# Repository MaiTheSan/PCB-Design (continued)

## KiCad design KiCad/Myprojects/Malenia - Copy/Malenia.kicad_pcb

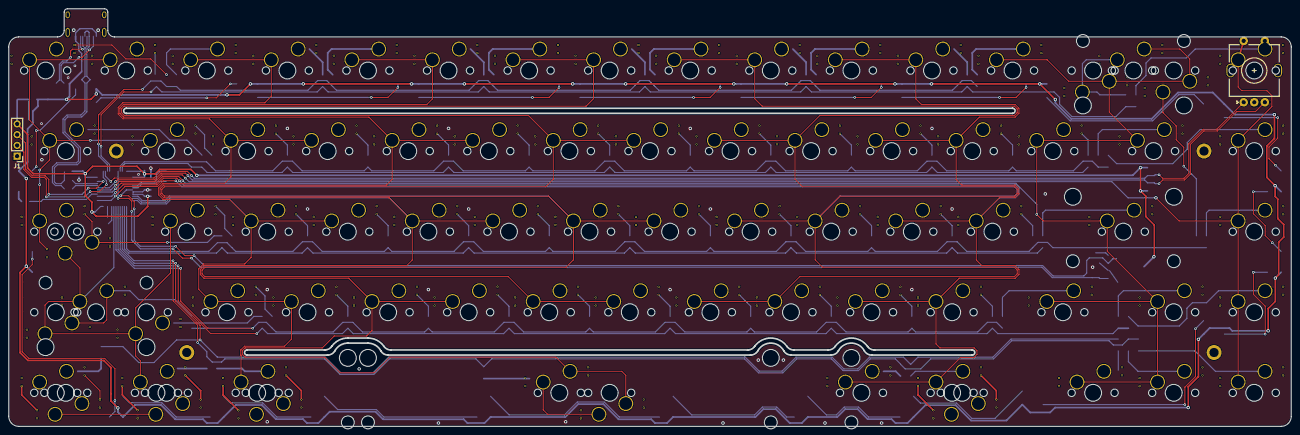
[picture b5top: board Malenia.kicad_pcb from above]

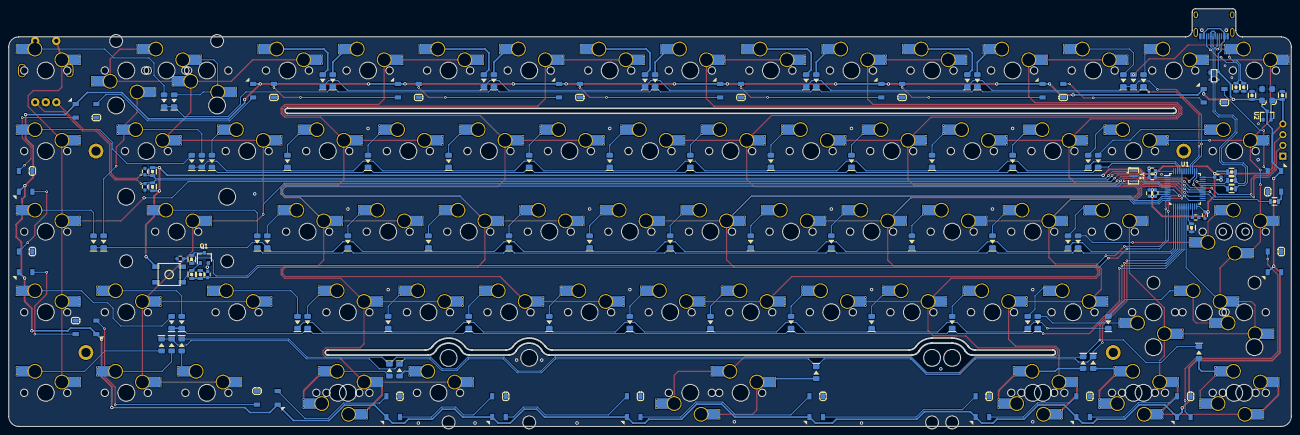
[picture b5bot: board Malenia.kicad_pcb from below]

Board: 2 copper layers, 303.2 x 98.7 mm, 207 parts (124 on the bottom side), 130 nets.

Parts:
C1, C2, C3, C4, C5, C9, C11, C12: 0.1uF; C_0603
C6: 1uF; C_0603
C7, C8: 1uF; CP_EIA-3216
C10: 10uF (5%); C_0603
C13: 4.7uF; C_0603
D1, D2, D3, D4, D5, D6, D7, D8, D9, D10, D11, D12, D13, D14, D15, D16, D17, D18, D19, D20, D21, D22, D23, D24, D25, D26, D27, D28, D29, D30, D31, D32, D33, D34, D35, D36, D37, D38, D39, D40, D41, D42, D43, D44, D45, D46, D47, D48, D49, D50, D51, D52, D53, D54, D55, D56, D57, D58, D59, D62, D65, D66, D67, D68, D69, D70, D71, D72, D73: SOD123; DIODE_1206_SawnsProjects
D75, D76, D77, D78, D79, D80, D81, D82, D83, D84, D85, D86, D87, D88, D89, D90, D91, D92, D93, D94, D95: WS2812B; LED_WS2812B_PLCC4_5.0x5.0mm_P3.2mm
H1, H2, H3, H4: MountingHole; MountingHole_2.2mm_M2_ISO7380_Pad
J1: Conn_01x04_Female; PinHeader_1x04_P2.54mm_Vertical
MX1, MX2, MX3, MX4, MX5, MX6, MX7, MX8, MX9, MX10, MX11, MX12, MX13, MX14, MX15, MX18, MX19, MX20, MX21, MX22, MX23, MX24, MX25, MX26, MX27, MX28, MX29, MX30, MX31, MX32, MX33, MX34, MX35, MX36, MX37, MX38, MX41, MX42, MX44, MX45, MX46, MX47, MX48, MX49, MX50, MX51, MX52, MX53, MX55, MX57, MX63, MX66, MX67, MX68, MX70, MX71, MX72, MX73: MX-1U; MXOnly-1U-Hotswap-Sawns
MX16, MX40, MX62, MX64, MX65: MX-1.5U; MXOnly-1.5U-Hotswap-Sawns
MX17, MX54: MX-1.75U; MXOnly-1.75U-Hotswap-Sawns
MX39: MX-2.25U; MXOnly-2.25U-Hotswap-ReversedStabilizers-Sawns
MX43, MX56, MX58, MX59, MX60, MX77, MX78: MX-1.25U; MXOnly-1.25U-Hotswap-Sawns
MX61: MX-6.25U; MXOnly-7U-Hotswap-Sawns
MX69: MX-6.25U; MXOnly-6.25U-Hotswap-ReversedStabilizers-Sawns
MX75: MX-2.25U; MXOnly-2.25U-Hotswap-Sawns
MX76: MX-2U; MXOnly-2U-Hotswap-Sawns
Q1: DTC123J; SC-59
R1, R2: 100K; R_0805
R3: 100R; R_0805
R4: 330k (1%); R_0805
R5: 1M (1%); R_0805
R6, R7: 22R; R_0805
R8, R9: 5.1k; R_0805
R10: 1.5k; R_0805
R11, R14: 330R; R_0805
R12, R13: 10k; R_0805
SW1: SW_Push; SKQGADE010
SW2: Rotary_Encoder_Switch; RotaryEncoder_Alps_EC11E-Switch_Vertical_H20mm_Center
U1: STM32F0X2/STM32F303; LQFP-48_7x7mm_P0.5mm
U2: MCP1700-3302E / MCP1703A-3302 (SOT23); SOT-23
U3: PRTR5V0U2X; SOT143B
USB1: HRO-TYPE-C-31-M-12-Type-C; HRO-TYPE-C-31-M-12-Assembly
Y1: 8Mhz; Resonator_SMD_muRata_CSTxExxV-3Pin_3.0x1.1mm

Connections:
+3V3: C1.1, C2.1, C3.1, C4.1, C5.1, C6.1, C8.1, J1.4, R2.1, R10.2, R12.1, R13.2, SW1.1, U1.1, U1.9, U1.24, U1.36, U1.48, U2.2
+5V: C7.1, D75.1, D76.1, D77.1, D78.1, D79.1, D80.1, D81.1, D82.1, D83.1, D84.1, D85.1, D86.1, D87.1, D88.1, D89.1, D90.1, D91.1, D92.1, D93.1, D94.1, D95.1, R1.1, U2.3, U3.4, USB1.2, USB1.11
/MCU/A+: R7.1, R10.1, U3.2, USB1.6, USB1.8
/MCU/A-: R6.2, U3.3, USB1.5, USB1.7
Boot0: C10.2, R4.1, R5.2, U1.44
C0: MX1.1, MX2.1, MX16.1, MX17.2, MX18.1, MX19.1, MX43.2, MX44.2, MX56.1, MX58.1, MX59.1, MX62.2, MX63.2, MX75.1, U1.19
C1: MX3.1, MX4.1, MX20.1, MX21.1, MX22.1, MX23.1, MX45.1, MX46.1, MX60.1, MX64.2, U1.12
C2: MX5.1, MX6.1, MX24.1, MX25.1, MX26.1, MX27.1, MX47.1, MX48.1, MX61.1, MX69.2, U1.11
C3: MX7.1, MX8.1, MX28.1, MX29.1, MX30.1, MX31.1, MX49.1, MX50.1, U1.10
C4: MX9.1, MX10.1, MX32.1, MX33.1, MX34.1, MX35.1, MX51.1, MX52.1, U1.25
C5: MX11.1, MX36.1, MX37.1, MX53.1, MX65.1, MX70.1, MX71.1, MX72.1, MX73.1, MX77.1, MX78.2, U1.27
C6: MX12.1, MX13.1, MX14.1, MX38.1, MX39.1, MX40.1, MX54.1, MX55.1, MX66.1, MX67.1, MX76.2, U1.29
C7: MX15.1, MX41.1, MX42.1, MX57.1, MX68.1, SW2.S2, U1.30
D+: R7.2, U1.33
D-: R6.1, U1.32
DOUT1: D83.2, D84.4
DOUT2: D92.2, D93.4
EC_A: C12.1, R13.1, SW2.A, U1.38
EC_B: C11.2, R12.2, SW2.B, U1.31
GND: C1.2, C2.2, C3.2, C4.2, C5.2, C6.2, C7.2, C8.2, C9.2, C10.1, C11.1, C12.2, C13.2, D75.3, D76.3, D77.3, D78.3, D79.3, D80.3, D81.3, D82.3, D83.3, D84.3, D85.3, D86.3, D87.3, D88.3, D89.3, D90.3, D91.3, D92.3, D93.3, D94.3, D95.3, J1.1, Q1.2, R1.2, R2.2, R5.1, R8.2, R9.1, R14.2, SW2.C, U1.8, U1.23, U1.35, U1.47, U2.1, U3.1, USB1.1, USB1.12, USB1.13, Y1.2
MX15: D40.2, MX15.2, SW2.S1
NRST: C9.1, R3.1, U1.7
unnamed: C13.1, U1.22
unnamed: D1.2, MX1.2
unnamed: D2.2, MX16.2
unnamed: D3.2, MX17.1, MX56.2
unnamed: D4.2, MX2.2
unnamed: D5.2, MX18.2
unnamed: D6.2, MX19.2
unnamed: D7.2, MX3.2
unnamed: D8.2, MX20.2
unnamed: D9.2, MX21.2
unnamed: D10.2, MX4.2
unnamed: D11.2, MX22.2
unnamed: D12.2, MX23.2
unnamed: D13.2, MX5.2
unnamed: D14.2, MX24.2
unnamed: D15.2, MX25.2
unnamed: D16.2, MX6.2
unnamed: D17.2, MX26.2
unnamed: D18.2, MX27.2
unnamed: D19.2, MX7.2
unnamed: D20.2, MX28.2
unnamed: D21.2, MX29.2
unnamed: D22.2, MX8.2
unnamed: D23.2, MX30.2
unnamed: D24.2, MX31.2
unnamed: D25.2, MX9.2
unnamed: D26.2, MX32.2
unnamed: D27.2, MX33.2
unnamed: D28.2, MX10.2
unnamed: D29.2, MX34.2
unnamed: D30.2, MX35.2
unnamed: D31.2, MX11.2
unnamed: D32.2, MX36.2
unnamed: D33.2, MX37.2
unnamed: D34.2, MX12.2
unnamed: D35.2, MX38.2
unnamed: D36.2, MX39.2
unnamed: D37.2, MX13.2, MX76.1
unnamed: D38.2, MX40.2
unnamed: D39.2, MX14.2
unnamed: D41.2, MX41.2
unnamed: D42.2, MX42.2
unnamed: D43.2, MX43.1, MX75.2
unnamed: D44.2, MX44.1
unnamed: D45.2, MX45.2
unnamed: D46.2, MX46.2
unnamed: D47.2, MX47.2
unnamed: D48.2, MX48.2
unnamed: D49.2, MX49.2
unnamed: D50.2, MX50.2
unnamed: D51.2, MX51.2
unnamed: D52.2, MX52.2
unnamed: D53.2, MX53.2
unnamed: D54.2, MX54.2
unnamed: D55.2, MX55.2
unnamed: D56.2, MX58.2, MX62.1
unnamed: D57.2, MX57.2
unnamed: D58.2, MX59.2, MX63.1
unnamed: D59.2, MX60.2, MX64.1
unnamed: D62.2, MX61.2, MX69.1
unnamed: D65.2, MX77.2
unnamed: D66.2, MX66.2
unnamed: D67.2, MX67.2
unnamed: D68.2, MX68.2
unnamed: D69.2, MX70.2
unnamed: D70.2, MX71.2
unnamed: D71.2, MX72.2
unnamed: D72.2, MX73.2
unnamed: D73.2, MX65.2, MX78.1
unnamed: D75.2, D76.4
unnamed: D76.2, D77.4
unnamed: D77.2, D78.4
unnamed: D78.2, D79.4
unnamed: D79.2, D80.4
unnamed: D80.2, D81.4
unnamed: D81.2, D82.4
unnamed: D82.2, D83.4
unnamed: D84.2, D85.4
unnamed: D85.2, D86.4
unnamed: D86.2, D87.4
unnamed: D87.2, D88.4
unnamed: D88.2, D89.4
unnamed: D89.2, D90.4
unnamed: D90.2, D91.4
unnamed: D91.2, D92.4
unnamed: D93.2, D94.4
unnamed: D94.2, D95.4
unnamed: Q1.1, R4.2, SW1.2
unnamed: Q1.3, R3.2
unnamed: R8.1, USB1.4
unnamed: R9.2, USB1.10
unnamed: R11.1, U1.28
unnamed: R14.1, U1.20
unnamed: U1.5, Y1.1
unnamed: U1.6, Y1.3
R0: D4.1, D10.1, D16.1, D22.1, D28.1, D37.1, D40.1, D69.1, U1.40
R1: D1.1, D7.1, D13.1, D19.1, D25.1, D31.1, D34.1, U1.39
R2: D5.1, D11.1, D17.1, D23.1, D29.1, D38.1, D41.1, D70.1, U1.45
R3: D2.1, D8.1, D14.1, D20.1, D26.1, D32.1, D35.1, U1.46
R4: D6.1, D12.1, D18.1, D24.1, D30.1, D39.1, D42.1, D71.1, U1.13
R5: D3.1, D9.1, D15.1, D21.1, D27.1, D33.1, D36.1, U1.14
R6: D44.1, D46.1, D48.1, D50.1, D52.1, D55.1, D57.1, D72.1, U1.17
R7: D43.1, D45.1, D47.1, D49.1, D51.1, D53.1, D54.1, U1.18
R8: D58.1, D62.1, D65.1, D67.1, D68.1, U1.15
R9: D56.1, D59.1, D66.1, D73.1, U1.16
RGB: D75.4, R11.2
SWCLK: J1.2, U1.37
SWDIO: J1.3, U1.34

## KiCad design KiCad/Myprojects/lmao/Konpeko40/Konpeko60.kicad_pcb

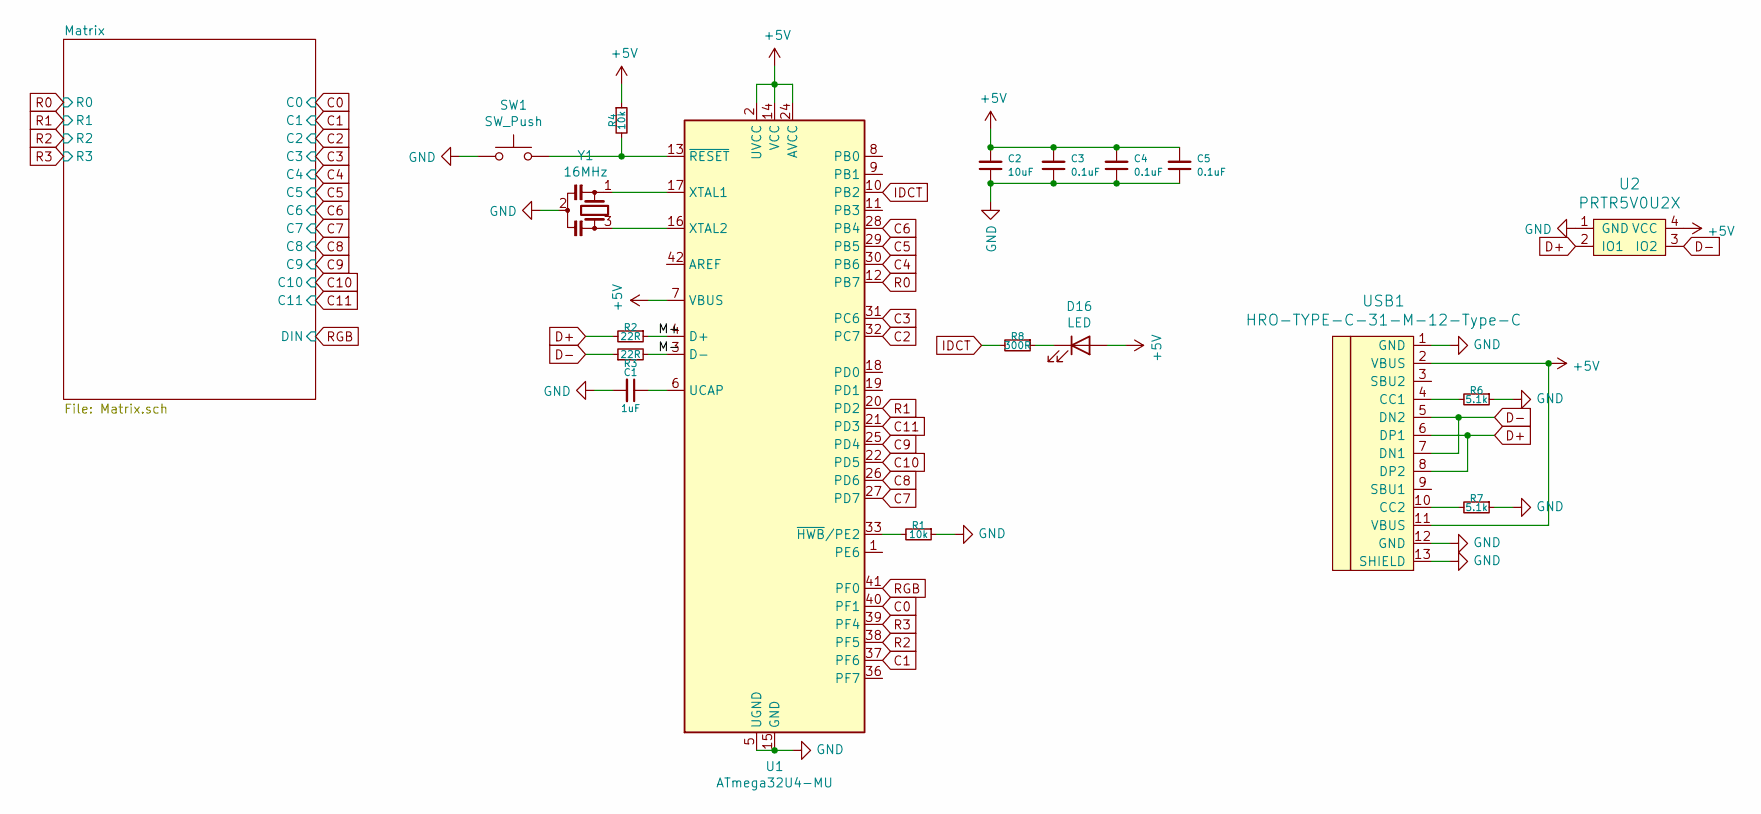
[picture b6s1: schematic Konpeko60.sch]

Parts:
C1: 1uF; C_0603
C2: 10uF; C_0603
C3, C4, C5: 0.1uF; C_0603
D16: LED; MXOnly-LEDONLY-FLIPPED
R1, R4: 10k; R_0603
R2, R3: 22R; R_0603
R6, R7: 5.1k; R_0603
R8: 300R; R_0603
SW1: SW_Push; SKQG-1155865-fix
U1: ATmega32U4-MU; QFN-44-1EP_7x7mm_P0.5mm_EP5.15x5.15mm_ThermalVias
U2: PRTR5V0U2X; SOT143B
USB1: HRO-TYPE-C-31-M-12-Type-C; HRO-TYPE-C-31-M-12-Assembly
Y1: 16MHz; Resonator_SMD_muRata_CSTxExxV-3Pin_3.0x1.1mm

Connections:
+5V: C2.2, C3.2, C4.2, C5.2, D16.2 (A), R4.1, U1.2 (UVCC), U1.7 (VBUS), U1.14 (VCC), U1.24 (AVCC), U1.34 (VCC), U1.44 (AVCC), U2.4 (VCC), USB1.2 (VBUS), USB1.11 (VBUS); also elsewhere on the board
/M+: R2.1, U1.4 (D+)
/M-: R3.2, U1.3 (D-)
C0: U1.40 (PF1); also elsewhere on the board
C1: U1.37 (PF6); also elsewhere on the board
C2: U1.32 (PC7); also elsewhere on the board
C3: U1.31 (PC6); also elsewhere on the board
C4: U1.30 (PB6); also elsewhere on the board
C5: U1.29 (PB5); also elsewhere on the board
C6: U1.28 (PB4); also elsewhere on the board
C7: U1.27 (PD7); also elsewhere on the board
C8: U1.26 (PD6); also elsewhere on the board
C9: U1.25 (PD4); also elsewhere on the board
C10: U1.22 (PD5); also elsewhere on the board
C11: U1.21 (PD3); also elsewhere on the board
D+: R2.2, U2.2 (IO1), USB1.6 (DP1), USB1.8 (DP2)
D-: R3.1, U2.3 (IO2), USB1.5 (DN2), USB1.7 (DN1)
GND: C1.2, C2.1, C3.1, C4.1, C5.1, R1.1, R6.1, R7.1, SW1.1, U1.5 (UGND), U1.15 (GND), U1.23 (GND), U1.35 (GND), U1.43 (GND), U1.45 (GND), U2.1 (GND), USB1.1 (GND), USB1.12 (GND), USB1.13 (SHIELD), Y1.2; also elsewhere on the board
IDCT: R8.2, U1.10 (PB2)
unnamed: C1.1, U1.6 (UCAP)
unnamed: D16.1 (K), R8.1
unnamed: R1.2, U1.33 (~HWB~/PE2)
unnamed: R4.2, SW1.2, U1.13 (~RESET)
unnamed: R6.2, USB1.4 (CC1)
unnamed: R7.2, USB1.10 (CC2)
unnamed: U1.16 (XTAL2), Y1.3
unnamed: U1.17 (XTAL1), Y1.1
R0: U1.12 (PB7); also elsewhere on the board
R1: U1.20 (PD2); also elsewhere on the board
R2: U1.38 (PF5); also elsewhere on the board
R3: U1.39 (PF4); also elsewhere on the board
RGB: U1.41 (PF0); also elsewhere on the board

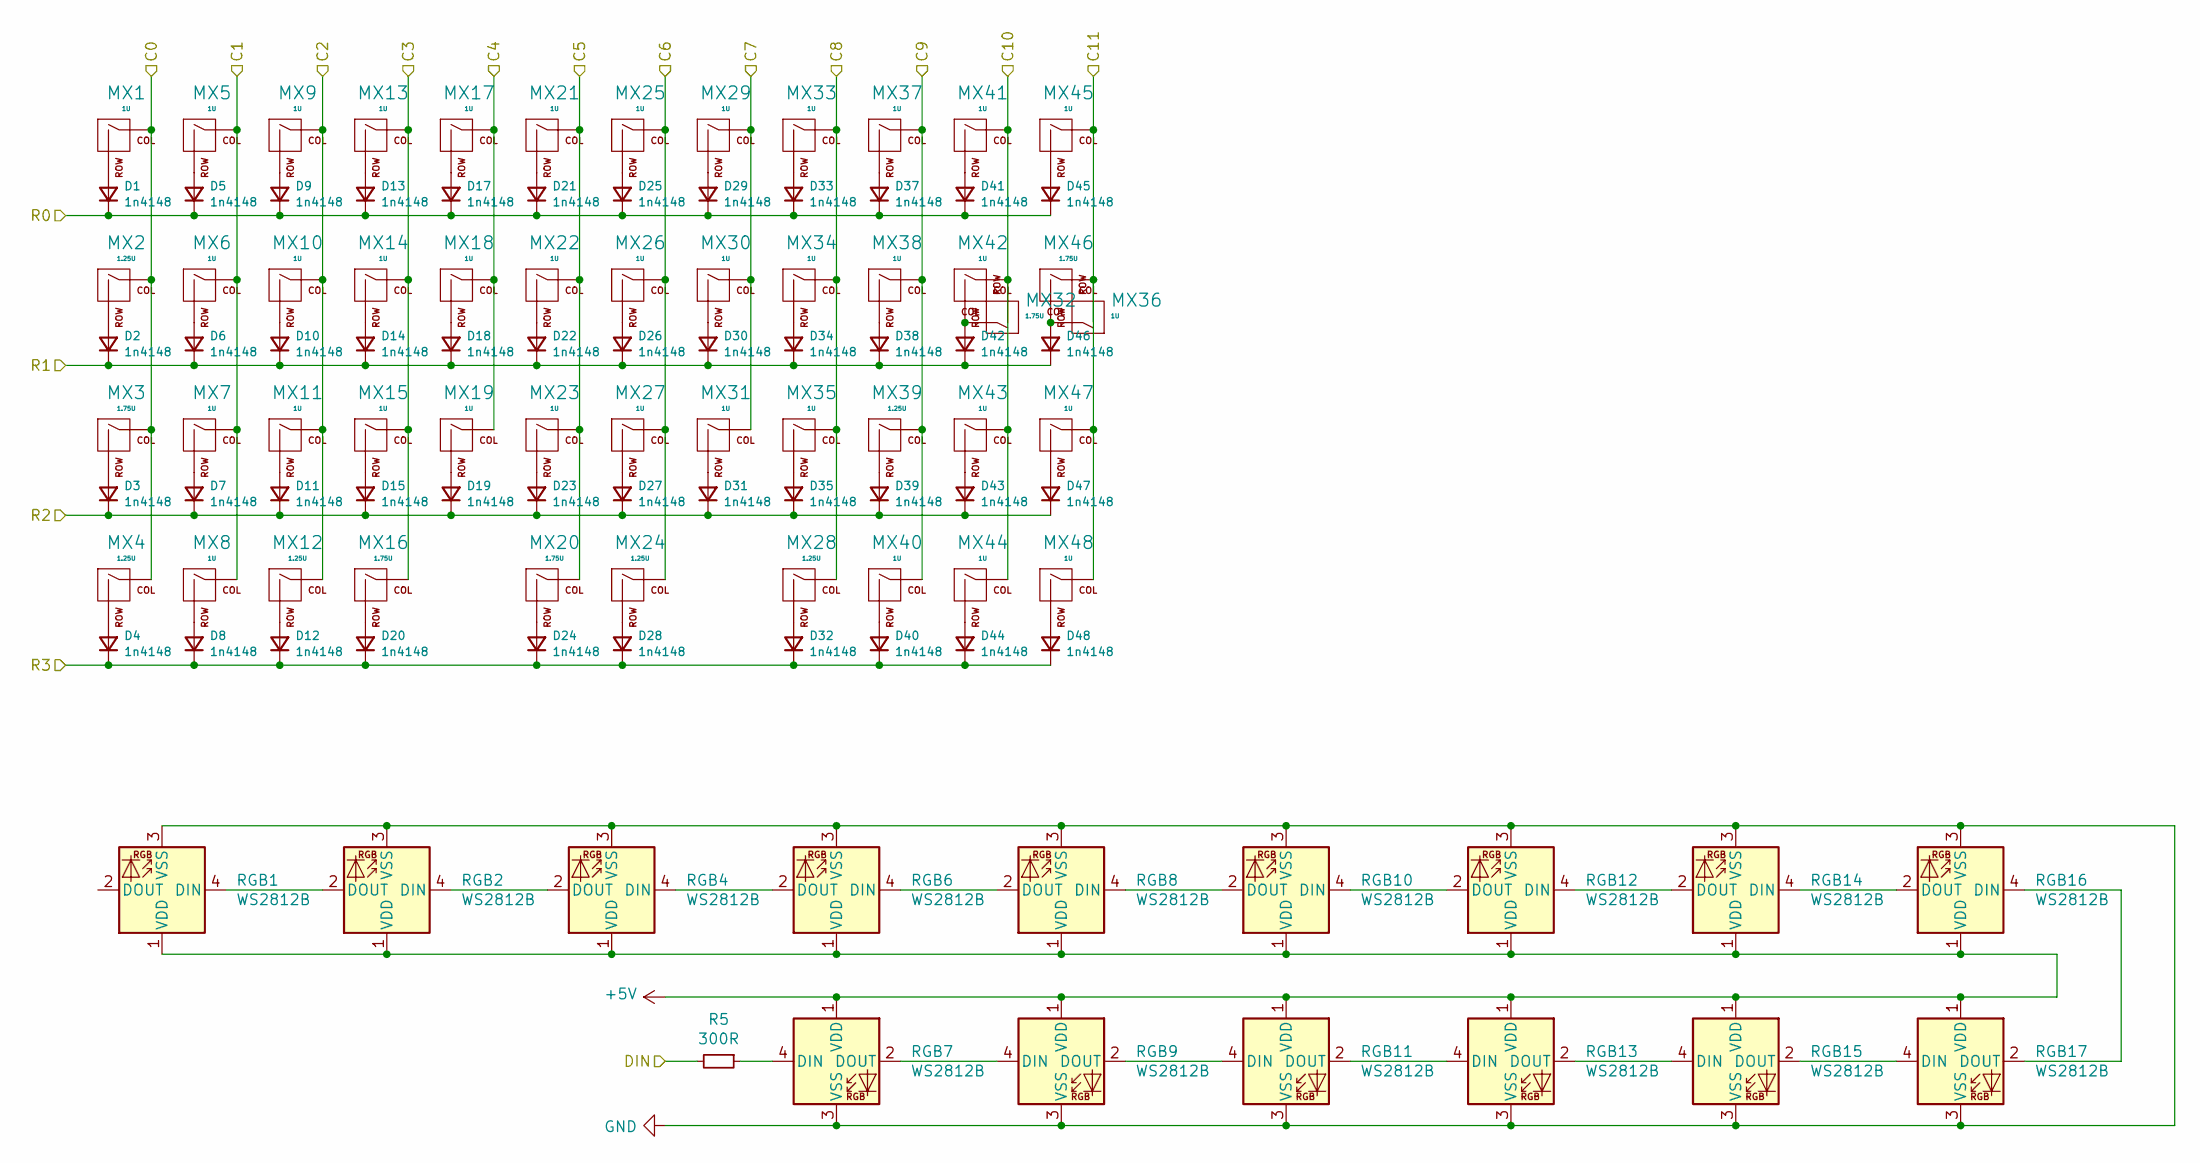
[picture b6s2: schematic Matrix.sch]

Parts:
D1, D2, D3, D4, D5, D6, D7, D8, D9, D10, D11, D12, D13, D14, D15, D17, D18, D19, D20, D21, D22, D23, D24, D25, D26, D27, D28, D29, D30, D31, D32, D33, D34, D35, D37, D38, D39, D40, D41, D42, D43, D44, D45, D46, D47, D48: 1n4148; DIODE_1206_SawnsProjects
MX1, MX5, MX6, MX7, MX8, MX9, MX10, MX11, MX13, MX14, MX15, MX17, MX18, MX19, MX21, MX22, MX23, MX25, MX26, MX27, MX29, MX30, MX31, MX33, MX34, MX35, MX36, MX37, MX38, MX40, MX41, MX42, MX43, MX44, MX45, MX47, MX48: 1U; MXOnly-1U-NoLED
MX2, MX4, MX12, MX24, MX28, MX39: 1.25U; MXOnly-1.25U-NoLED
MX3, MX16, MX20, MX32, MX46: 1.75U; MXOnly-1.75U-NoLED
R5: 300R; R_0805
RGB1, RGB2, RGB4, RGB6, RGB7, RGB8, RGB9, RGB10, RGB11, RGB12, RGB13, RGB14, RGB15, RGB16, RGB17: WS2812B; LED_WS2812B_PLCC4_5.0x5.0mm_P3.2mm

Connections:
+5V: RGB1.1 (VDD), RGB2.1 (VDD), RGB4.1 (VDD), RGB6.1 (VDD), RGB7.1 (VDD), RGB8.1 (VDD), RGB9.1 (VDD), RGB10.1 (VDD), RGB11.1 (VDD), RGB12.1 (VDD), RGB13.1 (VDD), RGB14.1 (VDD), RGB15.1 (VDD), RGB16.1 (VDD), RGB17.1 (VDD); also elsewhere on the board
C0: MX1.1 (COL), MX2.1 (COL), MX3.1 (COL), MX4.1 (COL); also elsewhere on the board
C1: MX5.1 (COL), MX6.1 (COL), MX7.1 (COL), MX8.1 (COL); also elsewhere on the board
C2: MX9.1 (COL), MX10.1 (COL), MX11.1 (COL), MX12.1 (COL); also elsewhere on the board
C3: MX13.1 (COL), MX14.1 (COL), MX15.1 (COL), MX16.1 (COL); also elsewhere on the board
C4: MX17.1 (COL), MX18.1 (COL), MX19.1 (COL); also elsewhere on the board
C5: MX20.1 (COL), MX21.1 (COL), MX22.1 (COL), MX23.1 (COL); also elsewhere on the board
C6: MX24.1 (COL), MX25.1 (COL), MX26.1 (COL), MX27.1 (COL); also elsewhere on the board
C7: MX29.1 (COL), MX30.1 (COL), MX31.1 (COL); also elsewhere on the board
C8: MX28.1 (COL), MX33.1 (COL), MX34.1 (COL), MX35.1 (COL); also elsewhere on the board
C9: MX37.1 (COL), MX38.1 (COL), MX39.1 (COL), MX40.1 (COL); also elsewhere on the board
C10: MX32.2 (ROW), MX41.1 (COL), MX42.1 (COL), MX43.1 (COL), MX44.1 (COL); also elsewhere on the board
C11: MX36.2 (ROW), MX45.1 (COL), MX46.1 (COL), MX47.1 (COL), MX48.1 (COL); also elsewhere on the board
GND: RGB1.3 (VSS), RGB2.3 (VSS), RGB4.3 (VSS), RGB6.3 (VSS), RGB7.3 (VSS), RGB8.3 (VSS), RGB9.3 (VSS), RGB10.3 (VSS), RGB11.3 (VSS), RGB12.3 (VSS), RGB13.3 (VSS), RGB14.3 (VSS), RGB15.3 (VSS), RGB16.3 (VSS), RGB17.3 (VSS); also elsewhere on the board
unnamed: D1.2 (A), MX1.2 (ROW)
unnamed: D2.2 (A), MX2.2 (ROW)
unnamed: D3.2 (A), MX3.2 (ROW)
unnamed: D4.2 (A), MX4.2 (ROW)
unnamed: D5.2 (A), MX5.2 (ROW)
unnamed: D6.2 (A), MX6.2 (ROW)
unnamed: D7.2 (A), MX7.2 (ROW)
unnamed: D8.2 (A), MX8.2 (ROW)
unnamed: D9.2 (A), MX9.2 (ROW)
unnamed: D10.2 (A), MX10.2 (ROW)
unnamed: D11.2 (A), MX11.2 (ROW)
unnamed: D12.2 (A), MX12.2 (ROW)
unnamed: D13.2 (A), MX13.2 (ROW)
unnamed: D14.2 (A), MX14.2 (ROW)
unnamed: D15.2 (A), MX15.2 (ROW)
unnamed: D17.2 (A), MX17.2 (ROW)
unnamed: D18.2 (A), MX18.2 (ROW)
unnamed: D19.2 (A), MX19.2 (ROW)
unnamed: D20.2 (A), MX16.2 (ROW)
unnamed: D21.2 (A), MX21.2 (ROW)
unnamed: D22.2 (A), MX22.2 (ROW)
unnamed: D23.2 (A), MX23.2 (ROW)
unnamed: D24.2 (A), MX20.2 (ROW)
unnamed: D25.2 (A), MX25.2 (ROW)
unnamed: D26.2 (A), MX26.2 (ROW)
unnamed: D27.2 (A), MX27.2 (ROW)
unnamed: D28.2 (A), MX24.2 (ROW)
unnamed: D29.2 (A), MX29.2 (ROW)
unnamed: D30.2 (A), MX30.2 (ROW)
unnamed: D31.2 (A), MX31.2 (ROW)
unnamed: D32.2 (A), MX28.2 (ROW)
unnamed: D33.2 (A), MX33.2 (ROW)
unnamed: D34.2 (A), MX34.2 (ROW)
unnamed: D35.2 (A), MX35.2 (ROW)
unnamed: D37.2 (A), MX37.2 (ROW)
unnamed: D38.2 (A), MX38.2 (ROW)
unnamed: D39.2 (A), MX39.2 (ROW)
unnamed: D40.2 (A), MX40.2 (ROW)
unnamed: D41.2 (A), MX41.2 (ROW)
unnamed: D42.2 (A), MX32.1 (COL), MX42.2 (ROW)
unnamed: D43.2 (A), MX43.2 (ROW)
unnamed: D44.2 (A), MX44.2 (ROW)
unnamed: D45.2 (A), MX45.2 (ROW)
unnamed: D46.2 (A), MX36.1 (COL), MX46.2 (ROW)
unnamed: D47.2 (A), MX47.2 (ROW)
unnamed: D48.2 (A), MX48.2 (ROW)
unnamed: R5.1, RGB7.4 (DIN)
unnamed: RGB1.4 (DIN), RGB2.2 (DOUT)
unnamed: RGB2.4 (DIN), RGB4.2 (DOUT)
unnamed: RGB4.4 (DIN), RGB6.2 (DOUT)
unnamed: RGB6.4 (DIN), RGB8.2 (DOUT)
unnamed: RGB7.2 (DOUT), RGB9.4 (DIN)
unnamed: RGB8.4 (DIN), RGB10.2 (DOUT)
unnamed: RGB10.4 (DIN), RGB12.2 (DOUT)
unnamed: RGB11.2 (DOUT), RGB13.4 (DIN)
unnamed: RGB9.2 (DOUT), RGB11.4 (DIN)
unnamed: RGB12.4 (DIN), RGB14.2 (DOUT)
unnamed: RGB13.2 (DOUT), RGB15.4 (DIN)
unnamed: RGB14.4 (DIN), RGB16.2 (DOUT)
unnamed: RGB15.2 (DOUT), RGB17.4 (DIN)
unnamed: RGB16.4 (DIN), RGB17.2 (DOUT)
R0: D1.1 (K), D5.1 (K), D9.1 (K), D13.1 (K), D17.1 (K), D21.1 (K), D25.1 (K), D29.1 (K), D33.1 (K), D37.1 (K), D41.1 (K), D45.1 (K); also elsewhere on the board
R1: D2.1 (K), D6.1 (K), D10.1 (K), D14.1 (K), D18.1 (K), D22.1 (K), D26.1 (K), D30.1 (K), D34.1 (K), D38.1 (K), D42.1 (K), D46.1 (K); also elsewhere on the board
R2: D3.1 (K), D7.1 (K), D11.1 (K), D15.1 (K), D19.1 (K), D23.1 (K), D27.1 (K), D31.1 (K), D35.1 (K), D39.1 (K), D43.1 (K), D47.1 (K); also elsewhere on the board
R3: D4.1 (K), D8.1 (K), D12.1 (K), D20.1 (K), D24.1 (K), D28.1 (K), D32.1 (K), D40.1 (K), D44.1 (K), D48.1 (K); also elsewhere on the board
RGB: R5.2; also elsewhere on the board

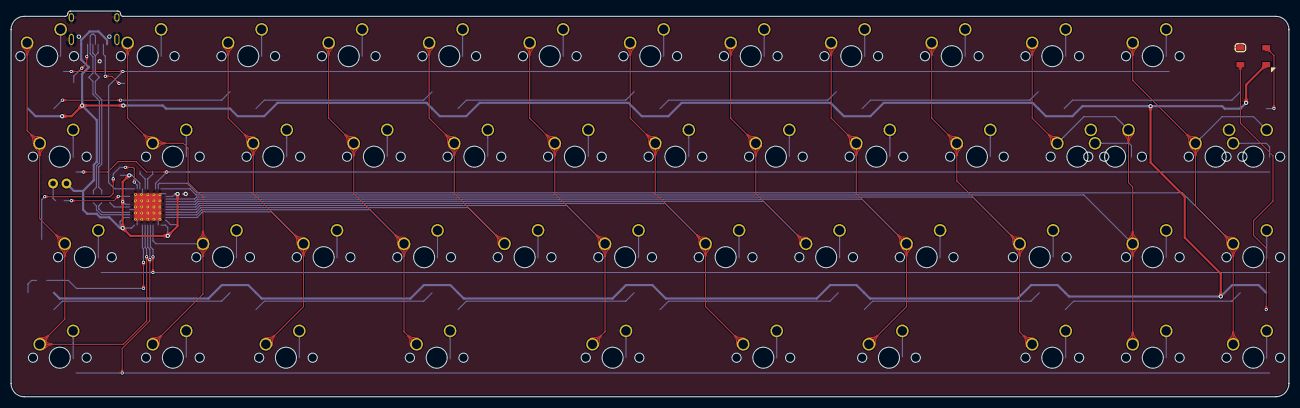
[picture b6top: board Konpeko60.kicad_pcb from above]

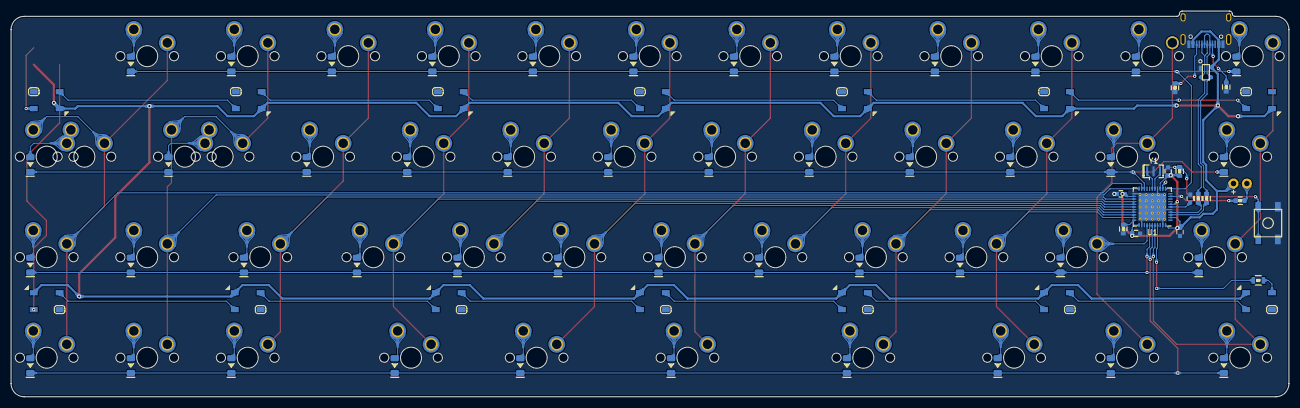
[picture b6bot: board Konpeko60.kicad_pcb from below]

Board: 2 copper layers, 242.2 x 73.1 mm, 128 parts (78 on the bottom side), 93 nets.
